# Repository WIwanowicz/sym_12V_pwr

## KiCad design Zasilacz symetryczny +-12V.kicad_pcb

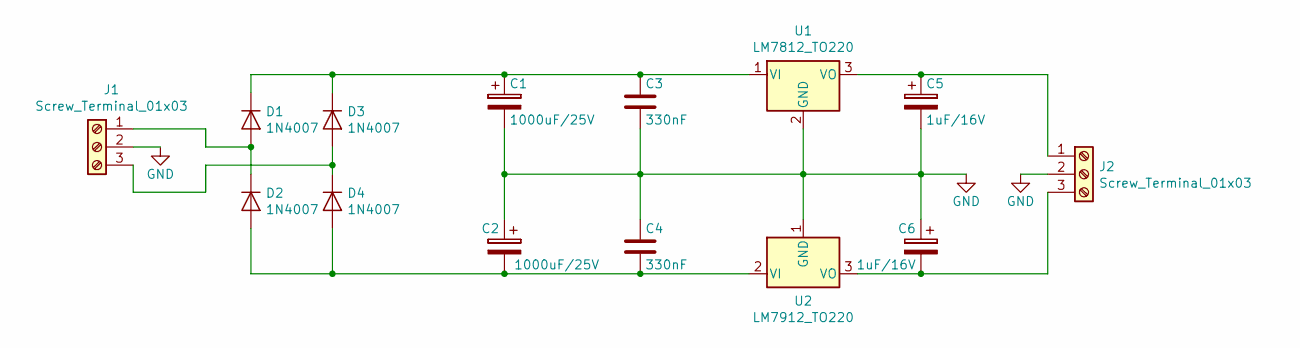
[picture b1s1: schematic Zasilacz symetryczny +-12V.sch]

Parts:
C1, C2: 1000uF/25V; CP_Radial_D10.0mm_P5.00mm
C3, C4: 330nF; C_Disc_D4.7mm_W2.5mm_P5.00mm
C5, C6: 1uF/16V; CP_Radial_D6.3mm_P2.50mm
D1, D2, D3, D4: 1N4007; D_DO-41_SOD81_P7.62mm_Horizontal
J1, J2: Screw_Terminal_01x03; TerminalBlock_Altech_AK300-3_P5.00mm
U1: LM7812_TO220; TO-220-3_Vertical
U2: LM7912_TO220; TO-220-3_Vertical

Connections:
GND: C1.2, C2.1, C3.2, C4.1, C5.2, C6.1, J1.2, J2.2, U1.2 (GND), U2.1 (GND)
unnamed: C1.1, C3.1, D1.1 (K), D3.1 (K), U1.1 (VI)
unnamed: C2.2, C4.2, D2.2 (A), D4.2 (A), U2.2 (VI)
unnamed: C5.1, J2.1, U1.3 (VO)
unnamed: C6.2, J2.3, U2.3 (VO)
unnamed: D1.2 (A), D2.1 (K), J1.1
unnamed: D3.2 (A), D4.1 (K), J1.3

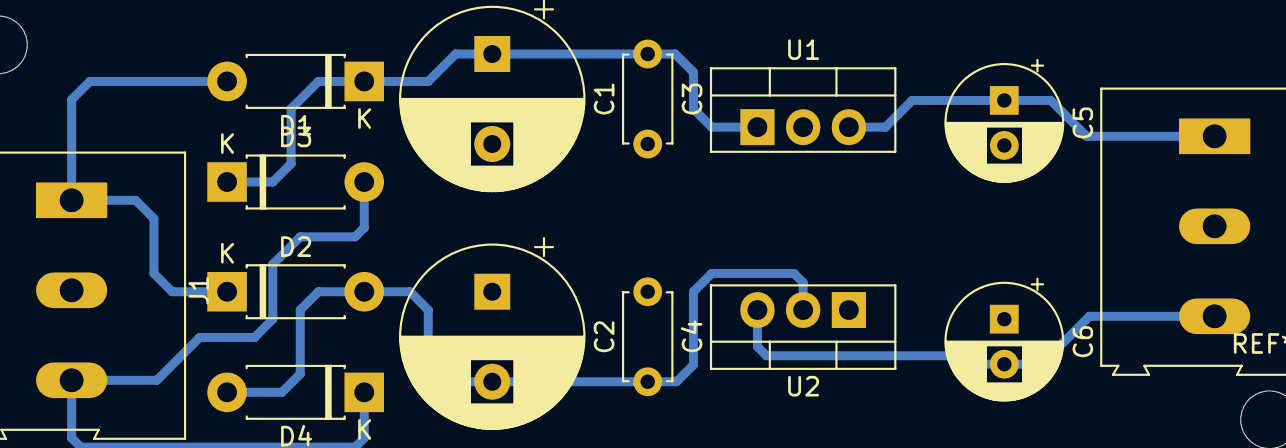
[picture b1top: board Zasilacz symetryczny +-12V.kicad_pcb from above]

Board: 2 copper layers, 14 parts (0 on the bottom side), 7 nets.

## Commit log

2020-06-15 you can use it to power your devices with +/-12V lol
